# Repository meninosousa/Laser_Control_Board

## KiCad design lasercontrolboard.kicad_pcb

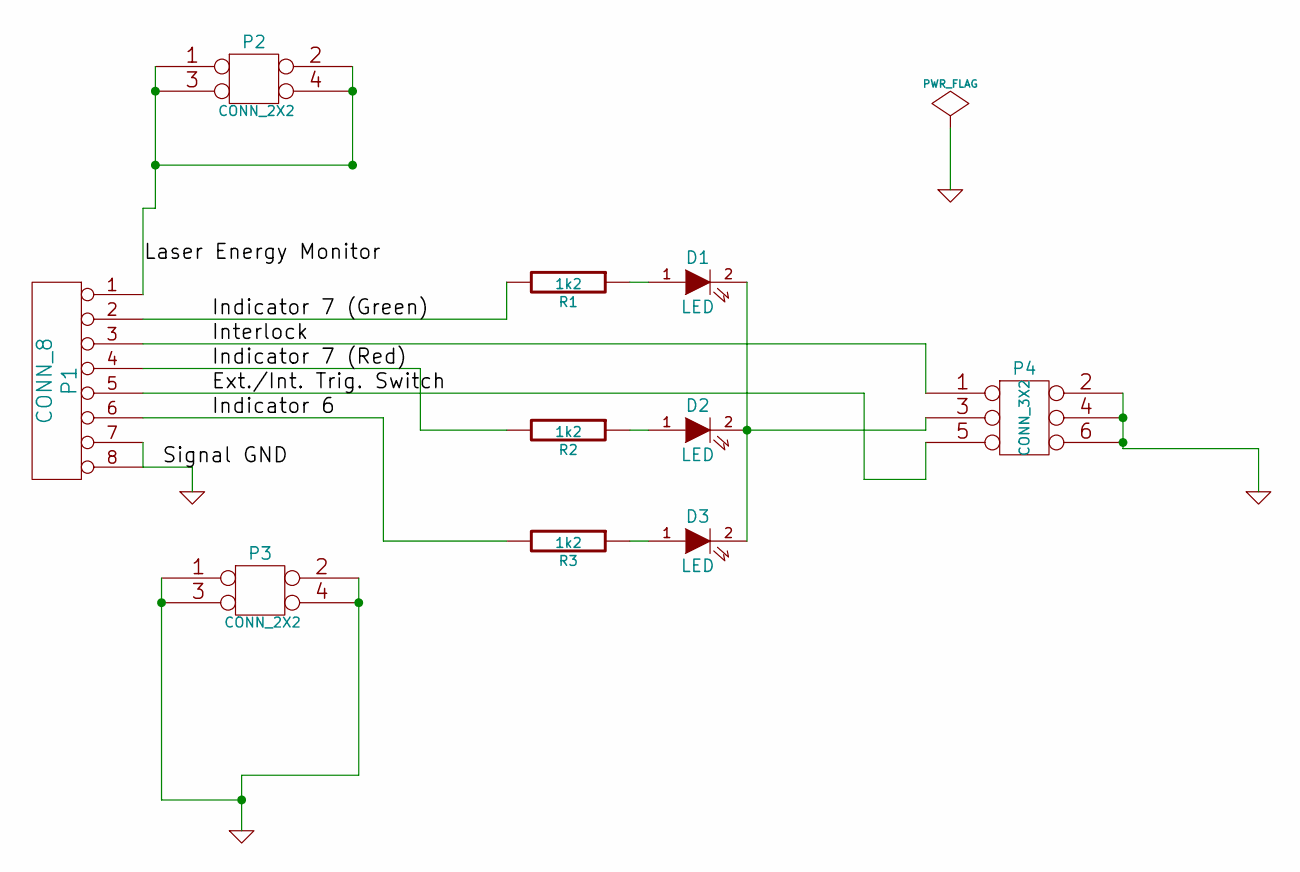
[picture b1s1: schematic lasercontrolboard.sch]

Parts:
D1, D2, D3: LED
P1: CONN_8
P2, P3: CONN_2X2
P4: CONN_3X2
R1, R2, R3: 1k2

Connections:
/Ext./Int. Trig. Switch: P1.5, P4.5
/Indicator 6: P1.6, R3.2
/Indicator 7 (Green): P1.2, R1.2
/Indicator 7 (Red): P1.4, R2.2
/Interlock: P1.3, P4.1
/Laser Energy Monitor: P1.1, P2.1, P2.2, P2.3, P2.4
GND: P1.7, P1.8, P3.1, P3.2, P3.3, P3.4, P4.2, P4.4, P4.6
unnamed: D2.1 (A), R2.1
unnamed: D1.1 (A), R1.1
unnamed: D1.2 (K), D2.2 (K), D3.2 (K), P4.3
unnamed: D3.1 (A), R3.1

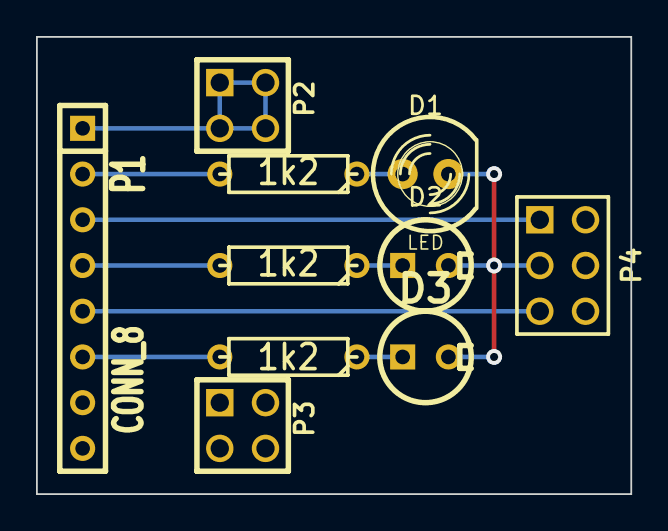
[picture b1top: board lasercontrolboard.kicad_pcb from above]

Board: 2 copper layers, 33.0 x 25.4 mm, 10 parts (0 on the bottom side), 11 nets.

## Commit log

2016-06-15 :tada: Added .gitattributes & .gitignore files
2016-06-15 test
    pls
